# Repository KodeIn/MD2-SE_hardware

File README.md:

# MD2-SE_hardware
Les fichiers CAD des PCB du mod Megadrive "Stream Edition"

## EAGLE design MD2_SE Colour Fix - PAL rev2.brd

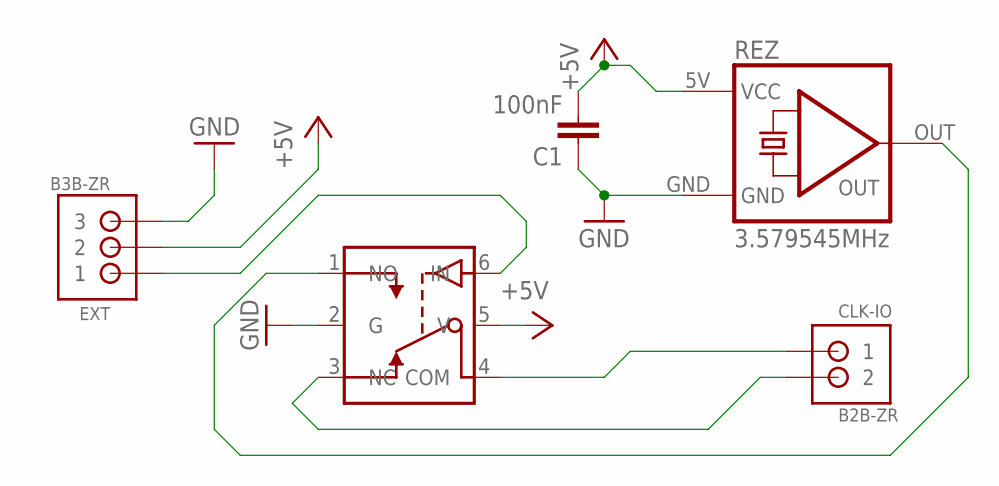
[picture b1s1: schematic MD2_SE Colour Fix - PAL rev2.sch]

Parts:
C1: 100nF; C0603K
CLK-IO: B2B-ZR
EXT: B3B-ZR
REZ: 3.579545MHz; DIL14S
SWITCH: TS5A3157EUT-T; SOT23-6

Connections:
+5V: C1.2, EXT.2, REZ.5V (VCC), SWITCH.5 (V)
GND: C1.1, EXT.3, REZ.GND, SWITCH.2 (G)
unnamed: EXT.1, SWITCH.6 (IN)
unnamed: CLK-IO.2, SWITCH.3 (NC)
NTSC: REZ.OUT, SWITCH.1 (NO)
OUT: CLK-IO.1, SWITCH.4 (COM)

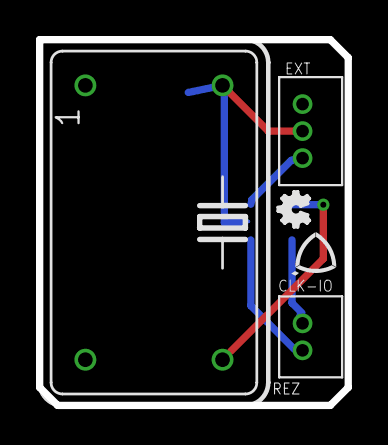
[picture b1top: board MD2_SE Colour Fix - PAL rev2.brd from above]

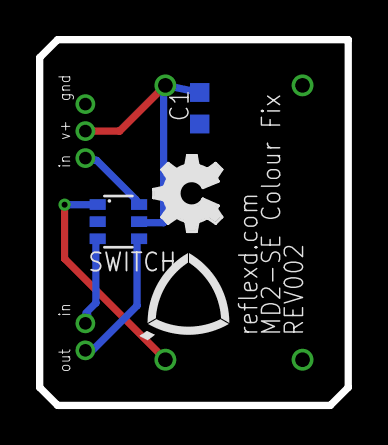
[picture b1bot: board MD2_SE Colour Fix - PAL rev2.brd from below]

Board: 2 copper layers, 17.1 x 20.3 mm, 9 parts (3 on the bottom side), 6 nets.

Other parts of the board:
U$1: LOGO-2.5MM
U$2: LOGO-5MM-BOTTOM
U$3: OSHW_FILLX70_NOTEXT
U$4: OSHW_FILLX150_NOTEXT

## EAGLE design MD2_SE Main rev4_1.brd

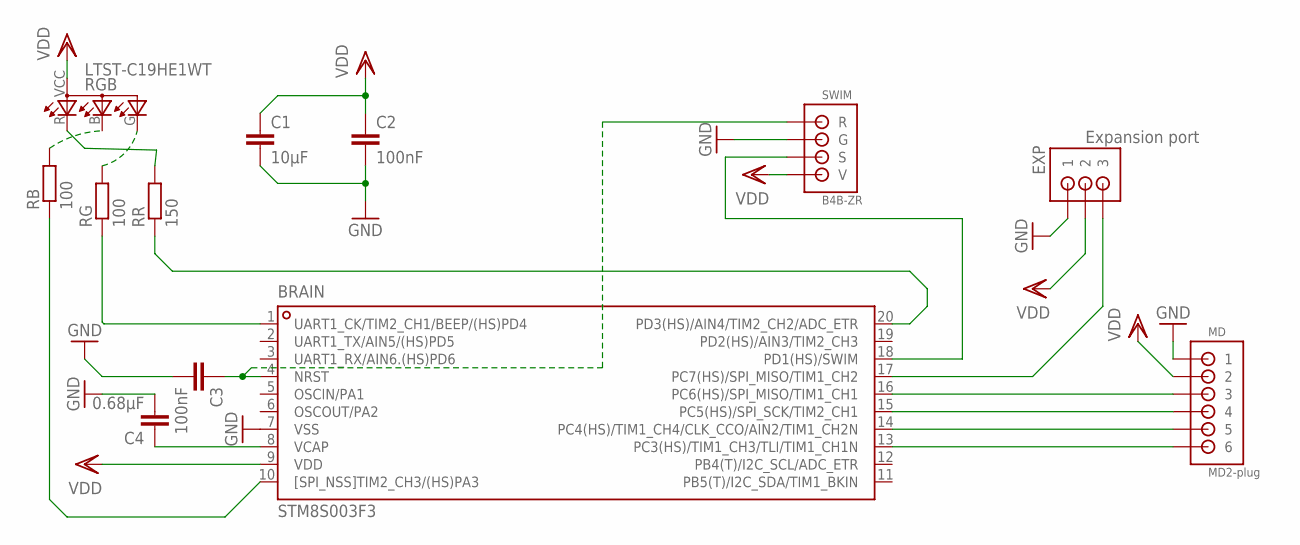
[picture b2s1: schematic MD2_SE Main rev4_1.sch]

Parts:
BRAIN: STM8S003F3; TSSOP20
C1: 10µF; C0603K
C2, C3: 100nF; C0603K
C4: 0.68µF; C0603K
EXP: Expansion port; B3B-ZR
MD: MD2-plug; B6B-ZR
RB: 100; R0603
RG: 100; R0603
RGB: LTST-C19HE1WT; 0606
RR: 150; R0603
SWIM: B4B-ZR

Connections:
BLUE$1: BRAIN.10 ([SPI_NSS]TIM2_CH3/(HS)PA3), RB.1
BLUE$2: RB.2, RGB.B (CBLUE)
EXP$1: BRAIN.17 (PC7(HS)/SPI_MISO/TIM1_CH2), EXP.3
GND: BRAIN.7 (VSS), C1.2, C2.2, C3.2, C4.2, EXP.1, MD.1, SWIM.GND (G)
GREEN$1: BRAIN.1 (UART1_CK/TIM2_CH1/BEEP/(HS)PD4), RG.1
GREEN$2: RG.2, RGB.G (CGREEN)
HZ$1: BRAIN.14 (PC4(HS)/TIM1_CH4/CLK_CCO/AIN2/TIM1_CH2N), MD.5
LANG$1: BRAIN.13 (PC3(HS)/TIM1_CH3/TLI/TIM1_CH1N), MD.6
RED$1: BRAIN.20 (PD3(HS)/AIN4/TIM2_CH2/ADC_ETR), RR.1
RED$2: RGB.R (CRED), RR.2
REGION$1: BRAIN.15 (PC5(HS)/SPI_SCK/TIM2_CH1), MD.4
RST_BTN$1: BRAIN.16 (PC6(HS)/SPI_MISO/TIM1_CH1), MD.3
SWIM$1: BRAIN.18 (PD1(HS)/SWIM), SWIM.SWIM (S)
SWM_RST$1: BRAIN.4 (NRST), C3.1, SWIM.RST (R)
VCAP$1: BRAIN.8 (VCAP), C4.1
VDD: BRAIN.9 (VDD), C1.1, C2.1, EXP.2, MD.2, RGB.VCC (V+), SWIM.VDD (V)

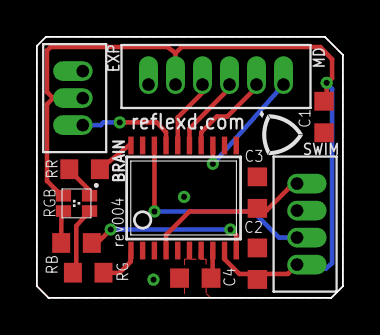
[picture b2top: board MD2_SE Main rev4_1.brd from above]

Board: 2 copper layers, 17.0 x 14.5 mm, 14 parts (0 on the bottom side), 16 nets.

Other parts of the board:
U$1: LOGO-2.5MM
U$2: LOGO-5MM-BOTTOM

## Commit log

2023-06-08 Ajout des fichiers MAIN Rev 4.01 (pcb principal)
    version encore sous eagle
2023-06-08 Ajout des fichiers Colour Fix rev 2
